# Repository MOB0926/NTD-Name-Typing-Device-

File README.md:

# NTD-Name-Typing-Device
 
This is my attempt at this project. I set out to get my hands on FREE components but then quickly realized this was no easy task. At first I stuck to the templete, but it got boring (quckly). I then put my brain to work and came to the briliant idea of a macropad that types my name. And so the NTD-V1 (Name-Typing-Device) was born.

# PCB
 
I mostly followed the guide for this but restarted it a few times as my own Ideas came into play.
 
I have an interest studying EE so I really tried to learn from this part. I found it was actually pretty fun, specially when creating the PCB and figuring out the puzzle of connecting the components.
 
I used KICAD as the guide instructed (Though I am new to it so it took quite a while)
 
I first built the guide board to figure it out. With what I learned, and some playing around (And a LOT of google) I slowly came up with my personal design incorporating the XIAO-RP2040, 6 switches, an OLED, and two LEDs (That I kinda forgot to remove so they are now official).

# CAD
 
The guide called for Fusion 360 but im on a low power laptop and have more experience in Onshape, so I designed my Case there.
 
I started with the bottom and designed it with the dimesnions of my pcb and added a hole for the usb-c where I designed it to be.

After the bottom was completed I designed the top with the key switch layout holes and holes for the Oled and LEDs. I also added some text and made sure the screw holes lined up properlly.

Edit - 1/7/26

I realized a few days later that ther was a mesage on my project asking for a 3d render of my project. 

At the time I was traveling so I could not edit but now that I can I realized that the case was ALL WRONG so I changed a few dimensions and now it works.
     
*Case Top

*Case Bottom

*3D Render

*3D Render with components (No Keycaps B/C I could only find stl files and they ruined the vibe + I put a lot of work into finding key switches and placing them)

# Firmware
 
For programing im mostly clueless, so I had a lot of help from Chat GPT. I honestly have no clue if this works untill it works or spits out a lot of errors.
 
The srcipt is in python, and will be used with CircuitPython and kmk to power the board.
 
Features:
- Inputs from the key switches
- Oled display - welcome message ("Welcome to NTD")
 
So far this will make it work but there is a lot of room for improvement once I am able to put some actual effort into the code.
  
# Final Build

# Design Flaws

As per every design there are flaws.
- Only types my name
- LED wrong footprint (Still works though)
- Case design in general
    - LED holes in wrong location
    - Inproper space for key-caps to fully go down and grab on
    - USB slot way to short (So the case is not fully screwed down to acomodate)
- No PCB mounting holes (Its fine but would be nicer)

# BOM
 
Required Materials:
- Seeed XIAO RP2040 
- MX-Style switches (x6)
- 0.91 inch OLED display
- Blank DSA keycaps (x6)
- SK6812 MINI-E LEDs (x2)
- M3x8mm screws (x4)
- M3x5mx4mm heatset inserts (x4)
- 3D Printed Case

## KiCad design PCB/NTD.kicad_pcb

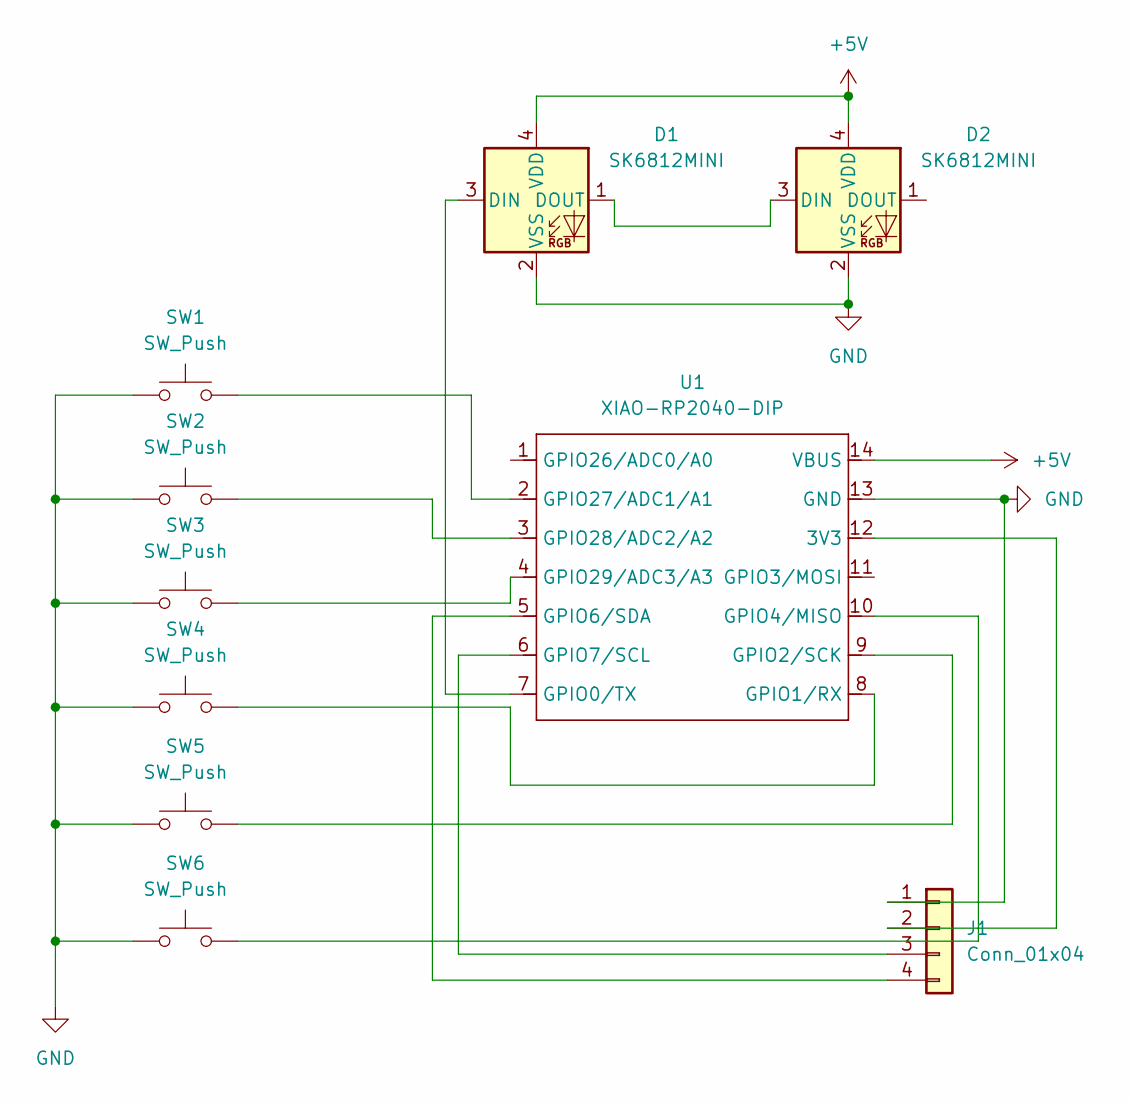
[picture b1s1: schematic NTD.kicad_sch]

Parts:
D1, D2: SK6812MINI; LED_SK6812MINI_PLCC4_3.5x3.5mm_P1.75mm
J1: Conn_01x04; SSD1306-0.91-OLED-4pin-128x32
SW1, SW2, SW3, SW4, SW5, SW6: SW_Push; SW_Cherry_MX_1.00u_PCB
U1: XIAO-RP2040-DIP

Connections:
+5V: D1.4 (VDD), D2.4 (VDD), U1.14 (VBUS)
GND: D1.2 (VSS), D2.2 (VSS), J1.1, SW1.1, SW2.1, SW3.1, SW4.1, SW5.1, SW6.1, U1.13 (GND)
unnamed: D1.3 (DIN), U1.7 (GPIO0/TX)
unnamed: D1.1 (DOUT), D2.3 (DIN)
unnamed: J1.2, U1.12 (3V3)
unnamed: J1.3, U1.6 (GPIO7/SCL)
unnamed: J1.4, U1.5 (GPIO6/SDA)
unnamed: SW4.2, U1.8 (GPIO1/RX)
unnamed: SW5.2, U1.9 (GPIO2/SCK)
unnamed: SW6.2, U1.10 (GPIO4/MISO)
unnamed: SW1.2, U1.2 (GPIO27/ADC1/A1)
unnamed: SW2.2, U1.3 (GPIO28/ADC2/A2)
unnamed: SW3.2, U1.4 (GPIO29/ADC3/A3)

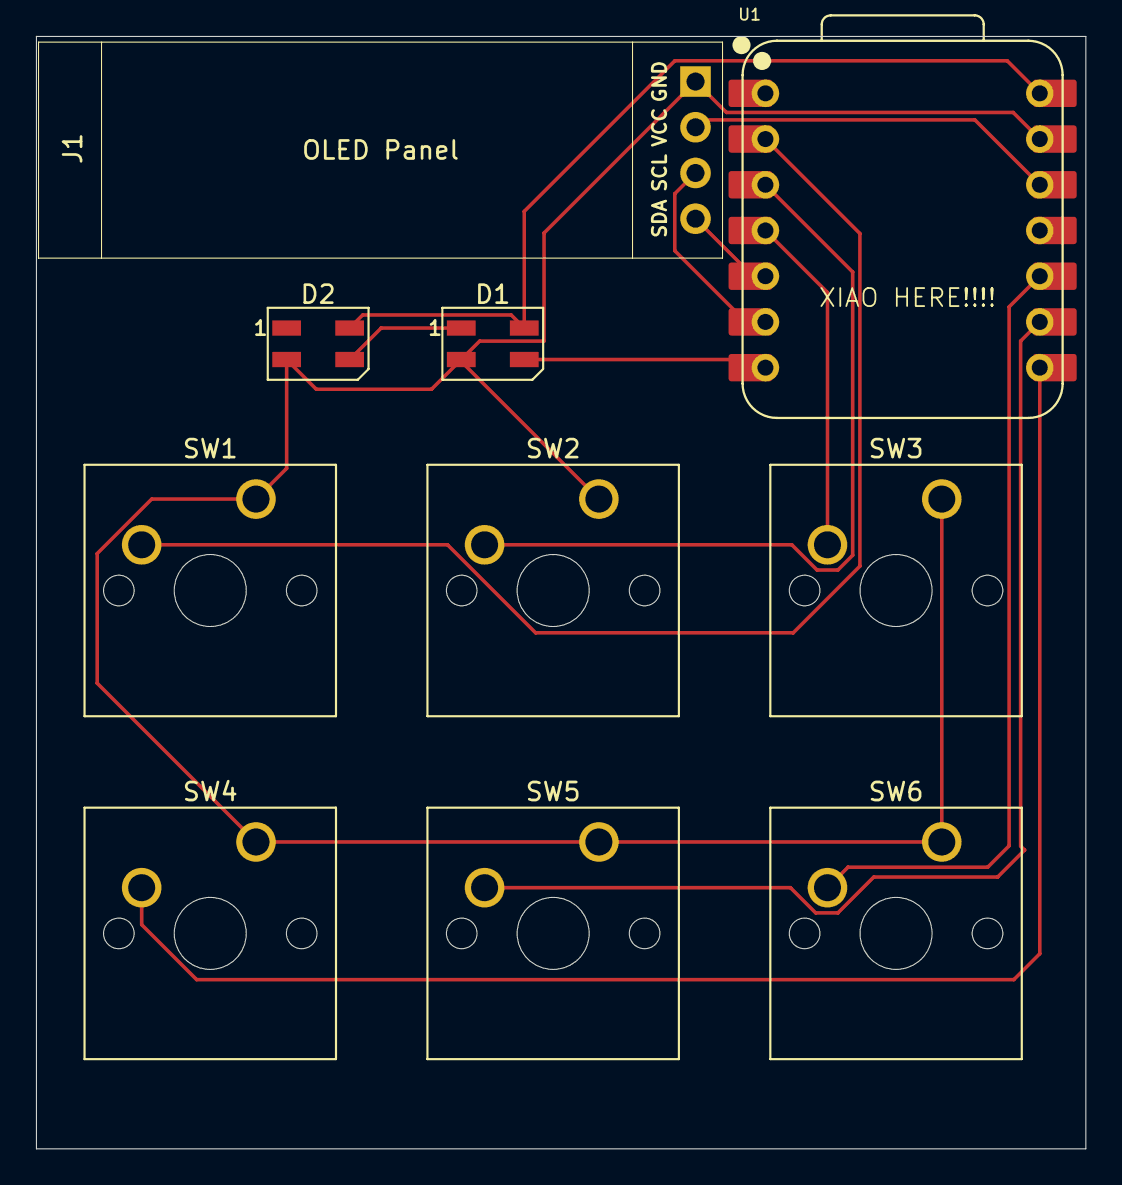
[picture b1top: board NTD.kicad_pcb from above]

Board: 2 copper layers, 58.3 x 61.8 mm, 10 parts (0 on the bottom side), 13 nets.

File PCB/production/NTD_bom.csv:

Designator,Footprint,Quantity,Value,LCSC Part #
"D1, D2",LED_SK6812MINI_PLCC4_3.5x3.5mm_P1.75mm,2,SK6812MINI,
J1,SSD1306-0.91-OLED-4pin-128x32,1,Conn_01x04,
"SW1, SW2, SW3, SW4, SW5, SW6",SW_Cherry_MX_1.00u_PCB,6,SW_Push,
U1,XIAO-RP2040-DIP,1,XIAO-RP2040-DIP,

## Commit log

2025-12-08 Create Create PCB + Schematic
2025-12-08 Rename Create PCB + Schematic to PCB + Schematic
2025-12-25 Create Firmware
2025-12-25 Rename Firmware to t
2025-12-25 Update t
2025-12-25 Rename t to f/m
2025-12-25 Create kmk
2025-12-25 Rename Firmware/kmk to Firmware/t/m
2025-12-25 Create k
2025-12-27 Create Case-Top
2025-12-27 Update print statement from 'Hello' to 'Goodbye'
2025-12-27 Rename Case/Case-Top to Case/trash/m
2025-12-28 Enhance README with design process and images
    Expanded the README to include details about the PCB design process, CAD software used, and images of the designs.
2025-12-28 Replace outdated images with new versions
    Updated images in the README to reflect the latest design changes.
2025-12-28 Revise README content and correct typos
    Updated README to improve clarity and fix typos.
2025-12-28 Update README with project insights and firmware info
    Expanded project description and added firmware details.
2026-01-07 New CAD
2026-01-07 Revise README with case updates and new images
    Updated the README to reflect changes made to the case dimensions and added images for the case top, bottom, and 3D render.
2026-01-07 Fix case dimensions and update 3D render images
    Corrected dimensions in the project case and updated images.
2026-01-07 Fix typos and enhance README structure
    Corrected typos and improved formatting in the README.
2026-01-08 Revise images and dimensions in README.md
    Updated image dimensions and added new images for case top, bottom, and 3D render sections in the README.
2026-01-08 Enhance 3D Render description in README
    Updated the 3D Render section with additional details about components and key switches.
2026-01-08 Fix README formatting and enhance firmware section
    Updated the README to correct formatting and clarify firmware information.
2026-01-17 New (Working) Script
2026-02-08 Final?
2026-02-08 silly me
2026-02-08 Fix image tag in README
    Updated README to fix image tag formatting.
